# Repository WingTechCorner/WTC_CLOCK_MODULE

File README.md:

# WTC_CLOCK_MODULE

# Project Purpose

* Make use of existing components I had in stock. In this case, a bunch of 40Mhz PLE(Plextronics) DIP-8, 4pin oscillators.
* Do voltage conversion from whatever the OSC uses to whatever the mainboard expects/users.
* Keep the footprint small.
* Use this as a sort of re-usable module going forward.

# Parts

| Part Count | Part Name                 | Package                 | Part                                       | Usage                                                                                 | Notes                                                                                                                                 |
| :----:     | :----                     | :----                   | :----                                      | :----                                                                                 | :----                                                                                                                                 |
| 1          | SN74LVC1T45               | SOT-23-6                | Single Channel Bidirectional Level Shifter | Takes the OSC clk_out and brings the voltage down to lower voltage.                   | 22 Ohm resistor has the DIR fixed so A goes to B only.                                                                                |
| 2          | C23345 (LCSC Part Number) | 0603 SMD                | 22 Ohm Resistor                            | Bridges signal pins to VCC                                                            |                                                                                                                                       |
| 1          | PLE-SQ3300-40.00Mhz OSC   | PDIP-8, 4pins, shortcan | 40Mhz 5V OSC                               | Plextronic's legacy/obsolete 40Mhz oscillator.                                        | Generates a 5V, 40Mhz clock signal. Enable tied to VCC via resistor. Output goes to SN74LVC1T45 to have voltage reduced.              |
| 1          | 1x4 header                | 2.54mm 1x4              | Right angle male header 4 pins             | Interface with parent module to provide a clock signal at the desired voltage levels. | Provides a "standard" way for me to add a clock source to another project board. Makes clock sources interchangable and/or re-usable. |

The assumption regarding the pinout of the OSC:

| Pin     | Function                                           |
| :-----: | :---------------                                   |
| 1       | Enable/Disable (current limit resistor tied to 5V) |
| 4       | GND                                                |
| 5       | Clock Output                                       |
| 8       | VCC (5V)                                           |

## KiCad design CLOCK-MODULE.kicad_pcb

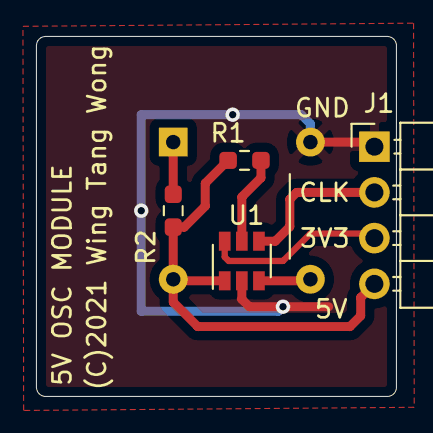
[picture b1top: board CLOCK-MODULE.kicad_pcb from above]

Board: 2 copper layers, 20.0 x 20.0 mm, 5 parts (1 on the bottom side), 7 nets.

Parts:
J1: Conn_01x04; PinHeader_1x04_P2.54mm_Horizontal
R1, R2: 22; R_0603_1608Metric_Pad0.98x0.95mm_HandSolder
U1: SN74LVC1T45DBV; SOT-23-6
X1: CXO_DIP8; Oscillator_DIP-8

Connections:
/3V3: J1.3, U1.6
/5V: J1.4, R1.2, R2.2, U1.1, X1.8
/CLK-TO-LS: U1.3, X1.5
/CLK_OUT: J1.2, U1.4
/GND: J1.1, U1.2, X1.4
/OSC-EN: R2.1, X1.1
unnamed: R1.1, U1.5

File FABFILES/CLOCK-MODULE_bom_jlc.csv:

"Comment","Designator","Footprint","LCSC Part #"
"Conn_01x04","J1","PinHeader_1x04_P2.54mm_Horizontal","no_part_number"
"22","R1,R2","R_0603_1608Metric_Pad0.98x0.95mm_HandSolder","C23345"
"SN74LVC1T45DBV","U1","SOT-23-6","no_part_number"
"CXO_DIP8","X1","Oscillator_DIP-8","C7843"

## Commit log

2021-09-10 Adding in CLOCK-MODULE kicad 5.x files as well as generated GBR/POS/BOM/XML files. csv files are setup for JLCPCB
2021-09-11 Adding more details to README.
2021-09-11 Cleaned up notes.

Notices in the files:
CLOCK-MODULE.kicad_pcb:
(C)2021 Wing Tang Wong
